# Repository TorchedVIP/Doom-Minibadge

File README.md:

# Doom Minibadge

## Project Description.
This is my Doom Minibadge! I have probably spent over 50 hours making this badge, debugging, and more; be aware it is held together with duct tape, zip ties, and hopes and dreams.
__NOTES:__
+ This badge is not done yet. I am still working on making it work. I will tell you where I got it wrong, and you can try to fix it. I am working on a solution as we speak.
+ There are LOTS of small parts, I only give you the required amount of parts, __YOU CANNOT LOSE THESE, I CANNOT REPLACE THEM__. Only take this if you are VERY good at soldering.
+ You will need bodge wire! (yayyyy... .  . .) I recommend 32 AWG; the minimum is 36 AWG, and the max is 26 AWG. I recommend 32, though, as it works so well for the display bodging.
+ Programming is super fun, I will have the files in this workspace, but you will need a Pi Pico set as a debugger, with Pico tester installed. I can help you flash it, so contact me over Discord.
+ Your badge just might not work! This has been such a hard project; I haven't been able to double-check every badge, you might just get one with a dead chip, tough luck. I have VERY few of these, so no replacements.
+ This is supposed to be fun, if you're not having fun soldering this, you shouldn't.

## Material list
1. Board 
2. Display (0.42") 
3. U2 (the real name is very long, I'm not pasting it here, but it's the chip-looking thing with 8 pins) 
4. Crystal 
5. Main Cap 
6. #6 Touch Pad Resistors 
7. #4 Display Caps 
8. Headers (there are only 2, 2, and 3 required; you do not need all the header spaces)
9. 32 AWG Wire (lots of it, I recommend 3 different colours; I used red, yellow, and blue)
10. __FLUX FLUX FLUX FLUX FLUX FLUX FLUX FLUX FLUX FLUX FLUX FLUX FLUX FLUX FLUX FLUX FLUX FLUX__

# Instructions
First, You're gonna want to solder top-side comps.

### Top
+ You will need the Touch Pad Resistors (TPR). Each TPR goes on the unmarked small pads on the board, they are all near their respective TP.
+ The main Cap is the only thing left on this side, that one is right next to the top right 3v3 pin. Do not short this one, we'll also be bodging some wires from here, later.
Now, let's flip to the back of the board for some easier parts to handle

### Bottom
+ You're going to want to solder U2 first, but be careful, the piece is bigger than the footprint. I recommend (committing an electrical sin) bending the legs backwards; they should be facing inwards, and U2 should be above the ground a little bit; that's fine, as we are putting on the headers later. The little indent on U2 should be oriented to the white arrow on the board (see image below) 
+ The crystal is a little bit harder, but not by much. It is found right below the FPC connector (see image below) and is non-polar. I recommend tilting it to a 45-degree angle, having one side facing towards you as you solder, or you could use rework or something. 
+ I'd like to point out really quickly that there are a lot of "missing parts" on the board: solder points with nothing on them. This is not intentional, but at this point, everything on the board is done (with the exception of headers), everything off it requires the remaining parts
+ Solder the headers on; you can do the entire row, but if you're doing just 2,2,3 headers, the headers should look like this image... 

## Display Bodge wires
One quick message to all you out there: the display bodging is not for the faint of heart, neither is connecting to the FPC pins, nor any of the rest of this. I recommend magnification for this section; I used +3.00 glasses, and it worked well. Anything else will do, too, but make sure the board is stationary. You will need a very fine tip for this stuff... and probably an afternoon.

### Caps
This one is by far the hardest, so buckle up.
To start, apply solder to pins 1-4 on the display; none of the others quite yet. You need to solder the display caps onto these pins, bridging 1-2 and 3-4 (see below)<br>
<br>

### Ordering
Now, solder pin 5 on the opposite side of the display, then 7, then 9, all the way to 13 (15 we'll talk about later). For these, you need a Bodge wire on every one of them. No exceptions. I recommend using a different coloured wire for these odd-numbered pins.<br>
<br>
All the even-numbered pins (besides 14 and 16; 16 we do later) need solder on them, on the opposite side of the odd-numbered ones. I recommend a different colour for these wires, too.<br>
<br>

Pins 15 and 16 need caps on them, but caps to the pin, then to bodge wires. Be careful the bodge wire does not directly touch the pin; best practice is to stand the cap up like a tombstone.<br>
<br>

### Attaching Bodge wires
   - Display pin 5 (VBAT) -> J3 PAD 5 (or 3v3)
   - Display pin 7 (VDD)  -> J3 PAD 7 (or 3v3)
   - Display pin 6 (VSS)  -> J3 PAD 6 (or GND)
   - Display pin 8 (BS1)  -> J3 PAD 6 (or GND)
   - Display pin 9 (CS)   -> J3 PAD 9
   - Display pin 10 (RES) -> J3 PAD 11
   - Display pin 11 (DC)  -> J3 PAD 10
   - Display pin 12 (SCLK)-> J3 PAD 12
   - Display pin 13 (SDIN)-> J3 PAD 13
   - Cap grounds (pin15, pin16 caps) -> J3 PAD 6 (or GND)

## Non-display Bodge Wires
For all these caps, you need to solder the 3V3 side. Make sure you get the right one so you don't short the badge; look at the schematics for this.<br>
+ Bodge wire from C1 to 3v3
+ Bodge wire from C2 to 3v3
+ Bodge wire from C3 to 3v3

# Flashing
You will need a Pico for this part.
## Part 1 — Build the Picoprobe (one-time, ~5 min)

1. Download `debugprobe_on_pico.uf2` from:
   https://github.com/raspberrypi/debugprobe/releases
   (older name: `picoprobe.uf2` — either works)

2. On the SPARE Pico: hold the BOOTSEL button while plugging in USB.

3. It mounts as a USB drive named `RPI-RP2`.

4. Drag `debugprobe_on_pico.uf2` onto that drive.

5. The Pico reboots. It is now a permanent SWD programmer. Done forever.

---

## Part 2 — What the Picoprobe Pins Do

On the Picoprobe (the spare Pico), these are the pins you use:

```
Picoprobe Pin | Role              | Goes to badge
--------------|-------------------|-------------------
GP2           | SWCLK (debug clk) | badge SWCLK (PROG)
GP3           | SWDIO (debug data)| badge SWDIO (PROG)
GND           | ground            | badge GND
3V3(OUT) pin36| 3.3V power        | badge 3.3V (optional, see below)
```

GP2 and GP3 are physical pins 4 and 5 on the Pico (top-left area).
GND is any of the Pico's GND pins (e.g. physical pin 3 or 38).
3V3(OUT) is physical pin 36.
## Part 2.2 - Breadboard
I __HIGHLY__ recommend using a breadboard for programming, use the same GND and 3V3 for every pin that needs it. It makes it so much easier. I also recommend having crocodile clips for debugging later.
## Part 3 — Wiring It Together (4 wires)

```
Picoprobe        Badge
---------        -----------------------------
GP2         -->  PROG1  (J1 pin 3)  = SWCLK
GP3         -->  PROG2  (J1 pin 4)  = SWDIO
GND         -->  GND
3V3(OUT)    -->  3V3                (powers the badge)
```

### Powering the badge — two choices:
- EASIEST: let the Picoprobe's 3V3(OUT) pin power the badge (wire above).
  Fine for a bare badge drawing little current.
- OR: plug the badge into the real minibadge host (it supplies 3.3V), and then
  only connect SWCLK, SWDIO, GND from the probe (leave 3V3 disconnected).

Do NOT power the badge from BOTH the probe's 3V3 AND the host at the same time.
Pick one power source.

## Part 4 — Flash (from WSL or Windows)

With the 4 wires connected and the badge powered:

```
picotool load -v doom_tiny_ssd1306.uf2 -f          # firmware
picotool load -v -t bin doom1.whx -o 0x10040000   # WAD data
picotool reboot                             # run it
```

Disconnect the probe. DOOM runs.

(Full build + picotool install steps are in FLASH_PLAN.md.)

## Troubleshooting

```
Symptom                          | Fix
---------------------------------|-------------------------------------------
"No accessible RP2040 device"    | Swap SWCLK/SWDIO wires; check GND; confirm
                                 | badge is powered (3.3V present)
"Unable to connect" / timeout    | Reflash debugprobe uf2; try another USB port
Probe not seen by PC at all      | Bad USB cable (power-only cable?) — use data
Connects but flash fails         | Lower adapter speed, re-seat wires
Badge dead after flash           | Check 3.3V, check RP2040 solder joints
```

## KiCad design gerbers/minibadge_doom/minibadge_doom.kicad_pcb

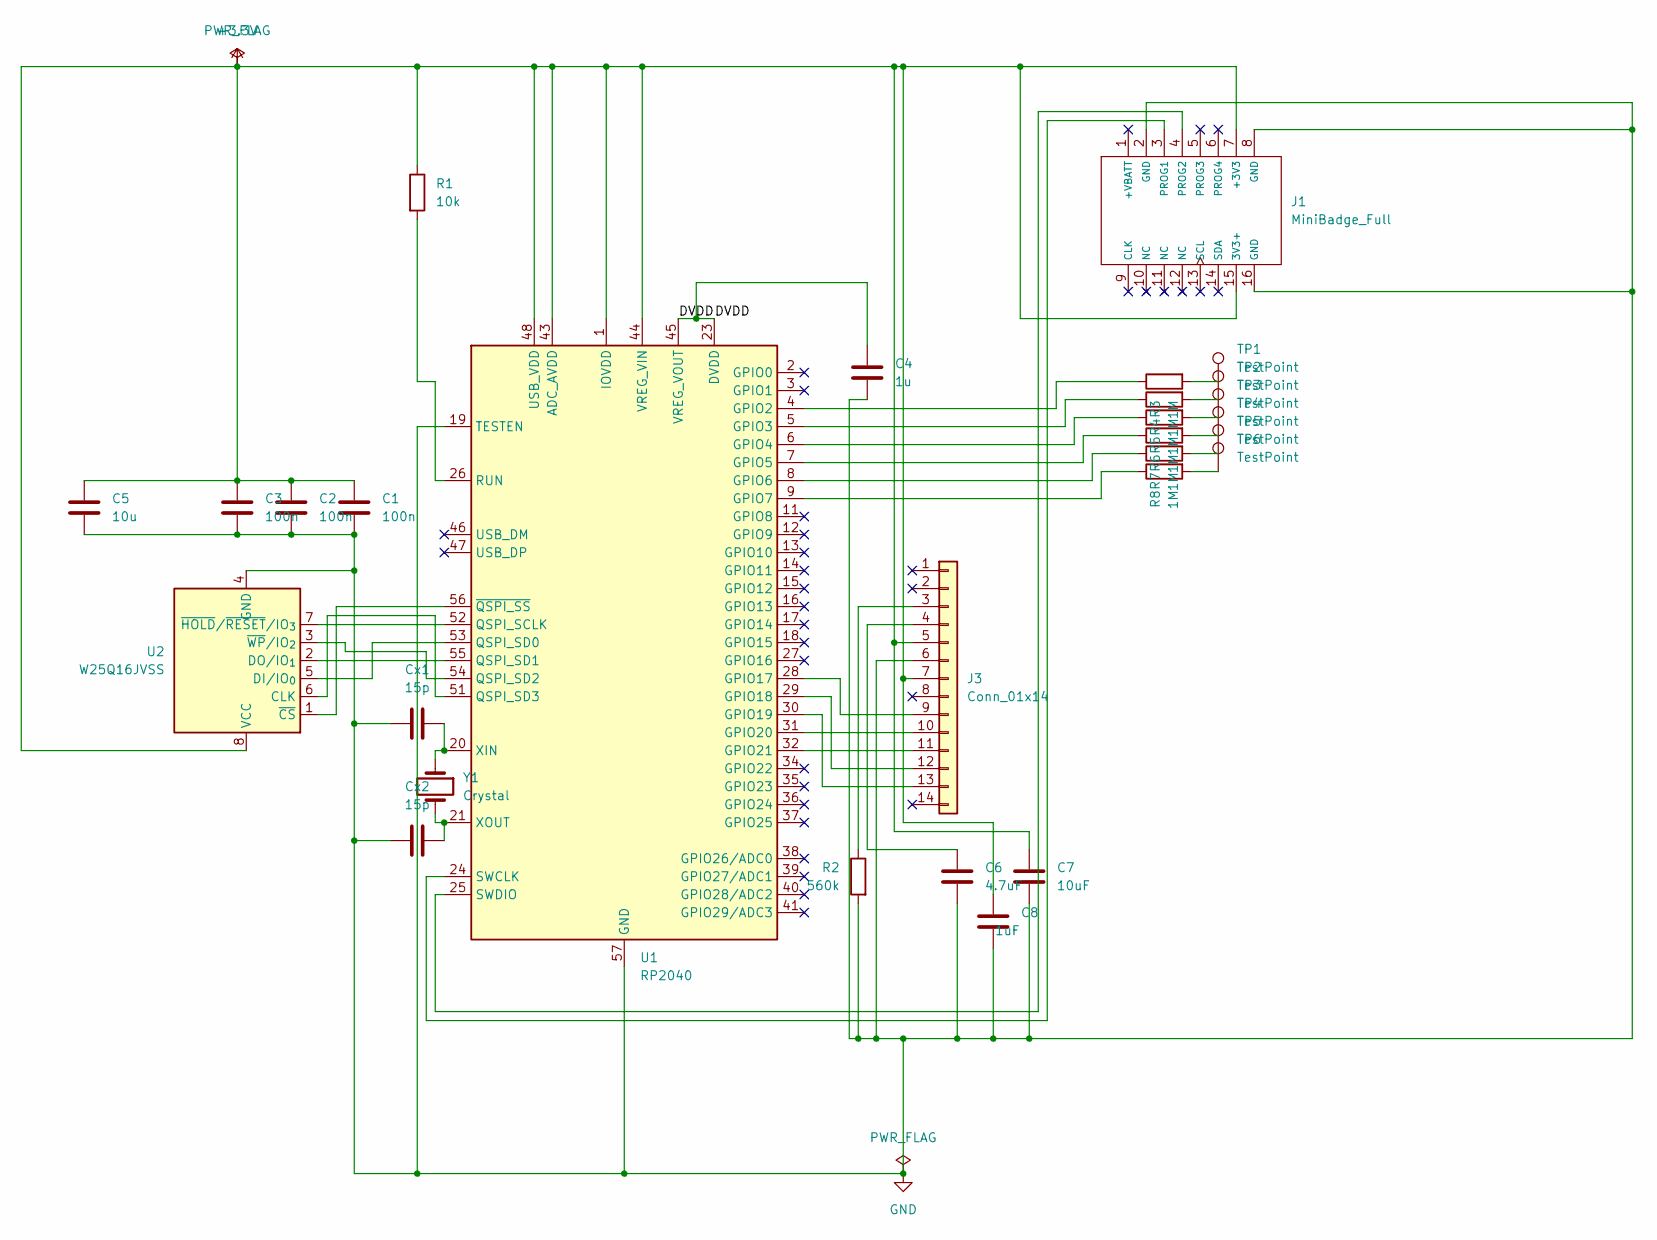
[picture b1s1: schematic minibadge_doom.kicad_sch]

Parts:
C1, C2, C3: 100n; C_0402_1005Metric
C4: 1u; C_0402_1005Metric
C5: 10u; C_0805_2012Metric
C6: 4.7uF; C_0402_1005Metric
C7: 10uF; C_0402_1005Metric
C8: 1uF; C_0402_1005Metric
Cx1, Cx2: 15p; C_0402_1005Metric
J1: MiniBadge_Full
J3: Conn_01x14; Hirose_FH12-14S-0.5SH_1x14-1MP_P0.50mm_Horizontal
R1: 10k; R_0402_1005Metric
R2: 560k; R_0402_1005Metric
R3, R4, R5, R6, R7, R8: 1M; R_0402_1005Metric
TP1, TP2, TP3, TP4, TP5, TP6: TestPoint; TestPoint_Pad_4.0x4.0mm
U1: RP2040; QFN-56-1EP_7x7mm_P0.4mm_EP3.2x3.2mm
U2: W25Q16JVSS; SOIC-8_3.9x4.9mm_P1.27mm
Y1: Crystal; Crystal_SMD_3215-2Pin_3.2x1.5mm

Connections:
+3.3V: C1.1, C2.1, C3.1, C5.1, C7.1, C8.1, J1.7 (+3V3), J1.15 (3V3+), J3.5, J3.7, R1.1, U1.1 (IOVDD), U1.10 (IOVDD), U1.22 (IOVDD), U1.33 (IOVDD), U1.42 (IOVDD), U1.43 (ADC_AVDD), U1.44 (VREG_VIN), U1.48 (USB_VDD), U1.49 (IOVDD), U2.8 (VCC)
/DVDD: C4.1, U1.23 (DVDD), U1.45 (VREG_VOUT), U1.50 (DVDD)
GND: C1.2, C2.2, C3.2, C4.2, C5.2, C6.2, C7.2, C8.2, Cx1.2, Cx2.2, J1.2 (GND), J1.8 (GND), J1.16 (GND), J3.6, R2.2, U1.19 (TESTEN), U1.57 (GND), U2.4 (GND)
unnamed: J1.3 (PROG1), U1.24 (SWCLK)
unnamed: J1.4 (PROG2), U1.25 (SWDIO)
unnamed: J3.3, R2.1
unnamed: C6.1, J3.4
unnamed: J3.9, U1.28 (GPIO17)
unnamed: J3.10, U1.31 (GPIO20)
unnamed: J3.11, U1.32 (GPIO21)
unnamed: J3.12, U1.29 (GPIO18)
unnamed: J3.13, U1.30 (GPIO19)
unnamed: R3.2, TP1.1 (1_1)
unnamed: R4.2, TP2.1 (1_1)
unnamed: R5.2, TP3.1 (1_1)
unnamed: R6.2, TP4.1 (1_1)
unnamed: R7.2, TP5.1 (1_1)
unnamed: R8.2, TP6.1 (1_1)
unnamed: R3.1, U1.4 (GPIO2)
unnamed: R4.1, U1.5 (GPIO3)
unnamed: R5.1, U1.6 (GPIO4)
unnamed: R6.1, U1.7 (GPIO5)
unnamed: R7.1, U1.8 (GPIO6)
unnamed: R8.1, U1.9 (GPIO7)
unnamed: U1.52 (QSPI_SCLK), U2.7 (~HOLD/~RESET/IO_{3})
unnamed: U1.53 (QSPI_SD0), U2.5 (DI/IO_{0})
unnamed: U1.55 (QSPI_SD1), U2.2 (DO/IO_{1})
unnamed: U1.54 (QSPI_SD2), U2.3 (~WP/IO_{2})
unnamed: U1.51 (QSPI_SD3), U2.6 (CLK)
unnamed: R1.2, U1.26 (RUN)
unnamed: Cx1.1, U1.20 (XIN), Y1.1
unnamed: Cx2.1, U1.21 (XOUT), Y1.2
unnamed: U1.56 (~QSPI_SS), U2.1 (~CS)

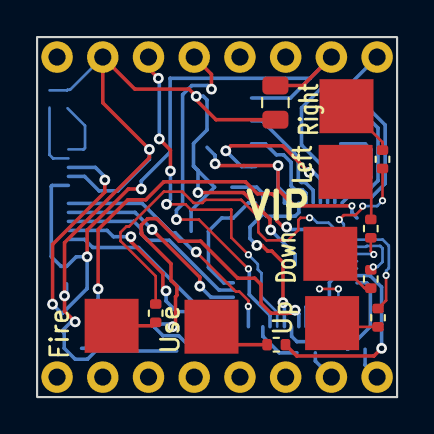
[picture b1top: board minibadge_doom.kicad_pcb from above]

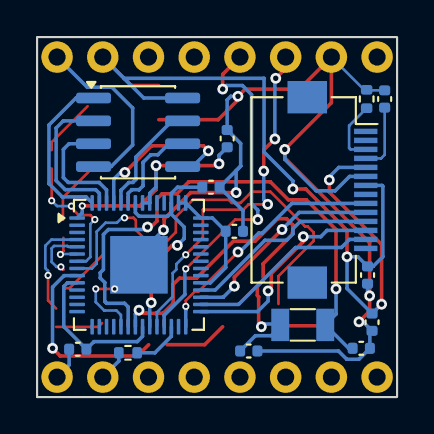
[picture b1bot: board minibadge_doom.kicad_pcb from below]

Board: 2 copper layers, 20.0 x 20.0 mm, 29 parts (15 on the bottom side), 33 nets.
